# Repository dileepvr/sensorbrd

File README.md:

These are kicad schematics and design files for PCBs used in the EMS
weather-balloon external sensor board project. These design files are
being released (as of this writing on the 30th of April, 2016) under
the CERN Open Hardware License v1.2 (see file LICENSE.txt for text of
the license).  All future versions of the CERN Open Hardware License
automatically apply.

For more information about the Nearspace balloon project, visit: https://eugenemakerspace.com/wiki/Sites/NearSpaceBalloon

The PCB uses an ATMEGA32u4 microcontroller to gather information from
various sensor modules, including a weather monitoring chip, and
several photodiodes with varying wavelength-range sensitivities that
together approximate a poor man's low-resolution spectrometer. The PCB
footprints for most modules are designed to match breakout boards
available from Adafruit Industries (see BOM file for details).

- Dileep V. Reddy

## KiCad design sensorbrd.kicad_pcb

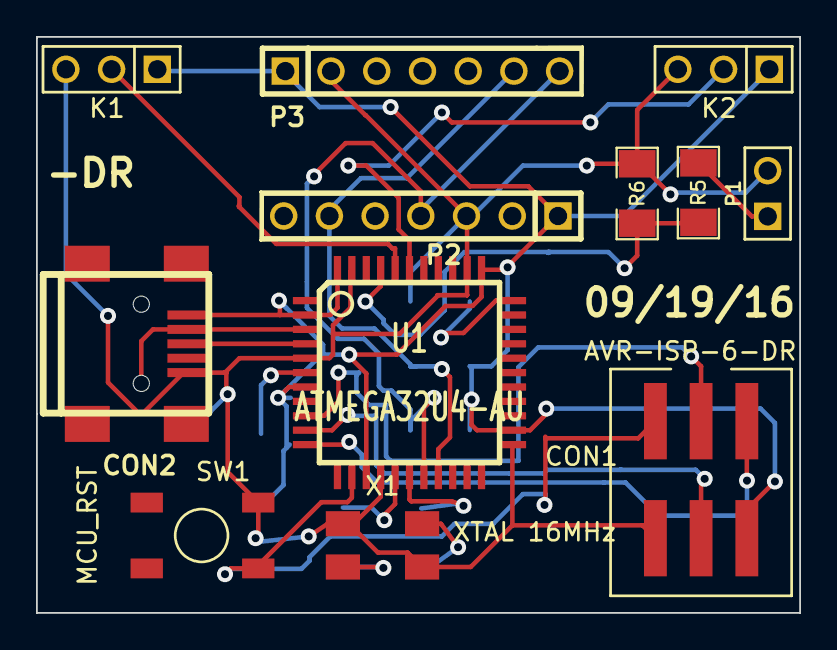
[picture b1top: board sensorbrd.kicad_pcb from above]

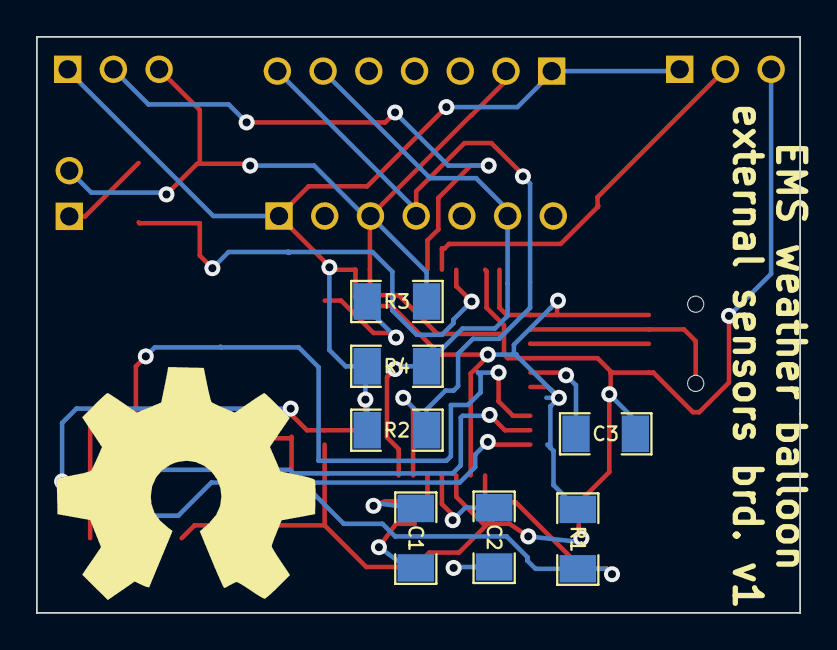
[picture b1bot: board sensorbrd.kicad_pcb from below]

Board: 2 copper layers, 42.4 x 32.0 mm, 19 parts (7 on the bottom side), 20 nets.

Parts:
C1, C2: 22pF; SM1206
C3: 1uF; SM1206
CON1: AVR-ISP-6-DR; AVR_6_SMD
CON2: USB-MINI-B; USB_MINI_B
K1: UV_SEN; PIN_ARRAY_3X1
K2: ALS_PT19; PIN_ARRAY_3X1
P1: SOLAR_PV; PIN_ARRAY_2X1
P2: BME280; PIN_ARRAY-7X1
P3: TSL2561; PIN_ARRAY-7X1
R1, R3, R6: 10K; SM1206
R2, R4: 4.7K; SM1206
R5: 1K; SM1206
SW1: MCU_RST; TACT_SW
U1: ATMEGA32U4-AU; TQFP44
X1: XTAL 16MHz; XTAL_6mmx3.5mm

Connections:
/D+: CON2.3, U1.4
/D-: CON2.2, U1.3
/RST: CON1.5, R1.2, SW1.4, U1.13
/SCK: P2.4, P3.7, R2.1, U1.18
/SDA: P2.6, P3.6, R4.1, U1.19
/SOL: R5.1, R6.2, U1.41
/UV: K1.2, U1.40
/VIS: K2.2, U1.39
GND: C3.1, CON1.6, CON2.5, K1.3, K2.3, P1.2, P2.3, P3.2, R3.2, R6.1, SW1.2, U1.5, U1.15, U1.23, U1.35, U1.43, X1.2, X1.4
unnamed: CON1.1, U1.11
unnamed: CON1.4, U1.10
unnamed: P1.1, R5.2
unnamed: C1.1, X1.3
unnamed: C2.1, X1.1
unnamed: C2.2, U1.16
unnamed: CON1.3, U1.9
unnamed: R3.1, U1.33
unnamed: C3.2, U1.6
unnamed: C1.2, U1.17
VCC: CON1.2, CON2.1, K1.1, K2.1, P2.1, P3.1, R1.1, R2.2, R4.2, U1.2, U1.7, U1.14, U1.24, U1.34, U1.44

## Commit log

2016-10-17 First commit after version 1.0 confirmed working.
2017-03-12 Arduino firmware code added.
